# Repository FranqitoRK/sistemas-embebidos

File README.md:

# sistemas-embebidos
Franco Augusto Maio

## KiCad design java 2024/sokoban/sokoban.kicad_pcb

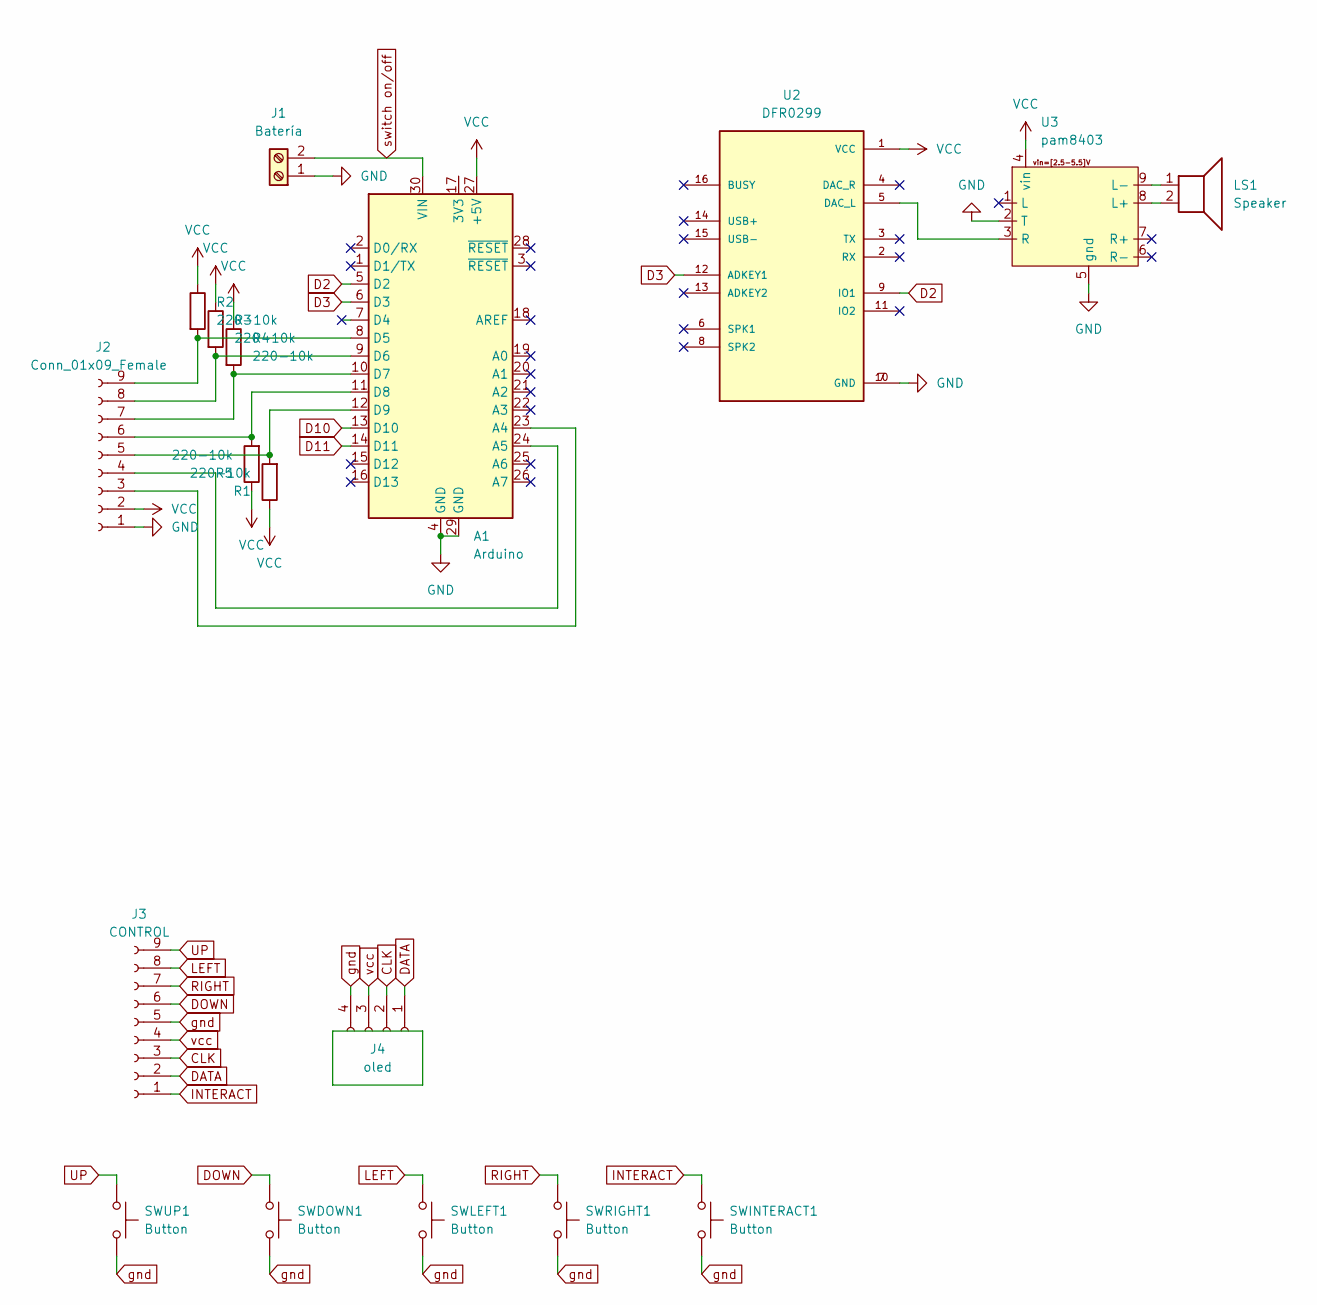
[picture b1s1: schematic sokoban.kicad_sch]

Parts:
A1: Arduino; Arduino_Nano
J1: Batería; TerminalBlock_bornier-2_P5.08mm
J2: Conn_01x09_Female; PinSocket_1x09_P2.54mm_Vertical
J3: CONTROL; DSUB-9_Female_Horizontal_P2.77x2.54mm_EdgePinOffset9.40mm
J4: oled; PinSocket_1x04_P2.54mm_Vertical
LS1: Speaker; TerminalBlock_bornier-2_P5.08mm
R1, R2, R3, R4, R5: 220-10k; R_Axial_DIN0207_L6.3mm_D2.5mm_P10.16mm_Horizontal
SWDOWN1: Button; SW_PUSH-12mm_Wuerth-430476085716
SWINTERACT1: Button; SW_PUSH-12mm_Wuerth-430476085716
SWLEFT1: Button; SW_PUSH-12mm_Wuerth-430476085716
SWRIGHT1: Button; SW_PUSH-12mm_Wuerth-430476085716
SWUP1: Button; SW_PUSH-12mm_Wuerth-430476085716
U2: DFR0299; MODULE_DFR0299; DigiKey_Part_Number 1738-1041-ND
U3: pam8403

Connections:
CLK: J3.3, J4.2
D2: A1.5 (D2), U2.9 (IO1)
D3: A1.6 (D3), U2.12 (ADKEY1)
D10: A1.13 (D10)
D11: A1.14 (D11)
DATA: J3.2, J4.1
DOWN: J3.6, SWDOWN1.1
GND: A1.4 (GND), A1.29 (GND), J1.1, J2.1, U2.7 (GND), U2.10 (GND), U3.2 (T), U3.5 (gnd)
INTERACT: J3.1, SWINTERACT1.1
LEFT: J3.8, SWLEFT1.1
unnamed: A1.23 (A4), J2.3
unnamed: A1.24 (A5), J2.4
unnamed: A1.8 (D5), J2.9, R2.2
unnamed: A1.9 (D6), J2.8, R3.2
unnamed: A1.10 (D7), J2.7, R4.2
unnamed: A1.11 (D8), J2.6, R5.2
unnamed: A1.12 (D9), J2.5, R1.2
unnamed: U2.5 (DAC_L), U3.3 (R)
unnamed: LS1.2, U3.8 (L+)
unnamed: LS1.1, U3.9 (L-)
RIGHT: J3.7, SWRIGHT1.1
UP: J3.9, SWUP1.1
VCC: A1.27 (+5V), J2.2, R1.1, R2.1, R3.1, R4.1, R5.1, U2.1 (VCC), U3.4 (vin)
gnd: J3.5, J4.4, SWDOWN1.2, SWINTERACT1.2, SWLEFT1.2, SWRIGHT1.2, SWUP1.2
switch on/off: A1.30 (VIN), J1.2
vcc: J3.4, J4.3

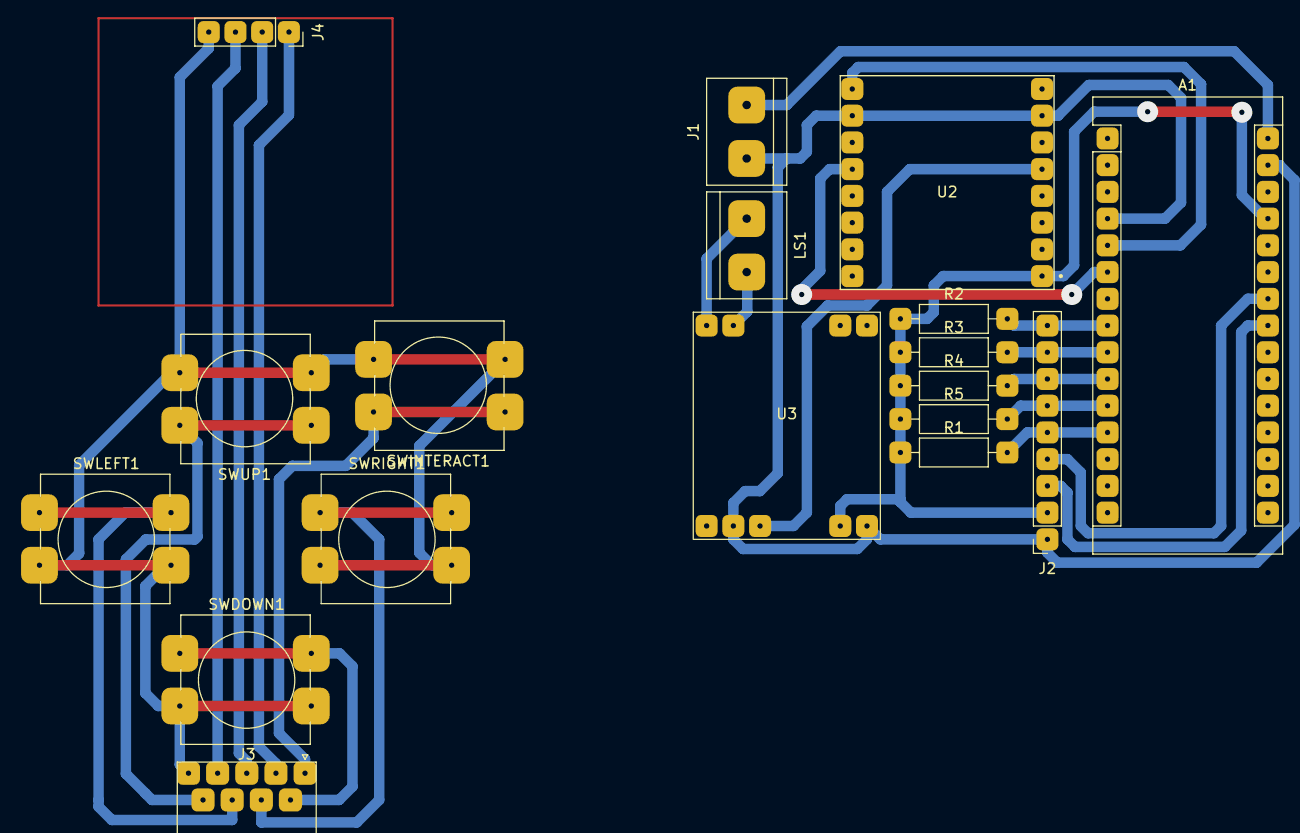
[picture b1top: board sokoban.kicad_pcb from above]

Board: 2 copper layers, 18 parts (0 on the bottom side), 24 nets.

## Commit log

2025-03-19 agregue nombre en readme
2025-03-21 Agrego ejercicio 1
2025-03-21 cambie el lenguaje a c pero no lo pude probar
2025-03-21 subo ej 2 y cambio ej 1
2025-03-21 agrego ej 3 incompleto
2025-03-26 ej 3 completo
2025-03-26 el ejercicio pedia 20 casos y de prueba estaba usando 5
2025-03-26 agrego ej 4
2025-03-26 ej4 v2
2025-03-26 ejercicio clase
2025-04-11 correccion ej en clase
2025-04-14 ej 11-4 funcionando, no tocar nada
2025-06-27 archivos java 2024
